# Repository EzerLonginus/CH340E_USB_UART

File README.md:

# CH340E_USB_UART
Simple USB to UART adapter using the CH340E

This board is a simple breakout for the CH340E USB to UART interface chip.  This chip is the less expensive option to the CP2102 or FTDI brand chip sets.  

## Purpose
I am looking to incorporate this chip in some designs, and I wanted to make confirm that this design will work.  It's pretty similar to the chips you would see on [AliExpress](https://www.aliexpress.us/item/3256805368897642.html) and [Ebay](https://www.ebay.com/itm/134189916686).

## Scematic

## Layout

## 3D Render

## Current State of Affairs
### Version 1
* Populate and test board
* Fix the inevitable issue that I missed during production

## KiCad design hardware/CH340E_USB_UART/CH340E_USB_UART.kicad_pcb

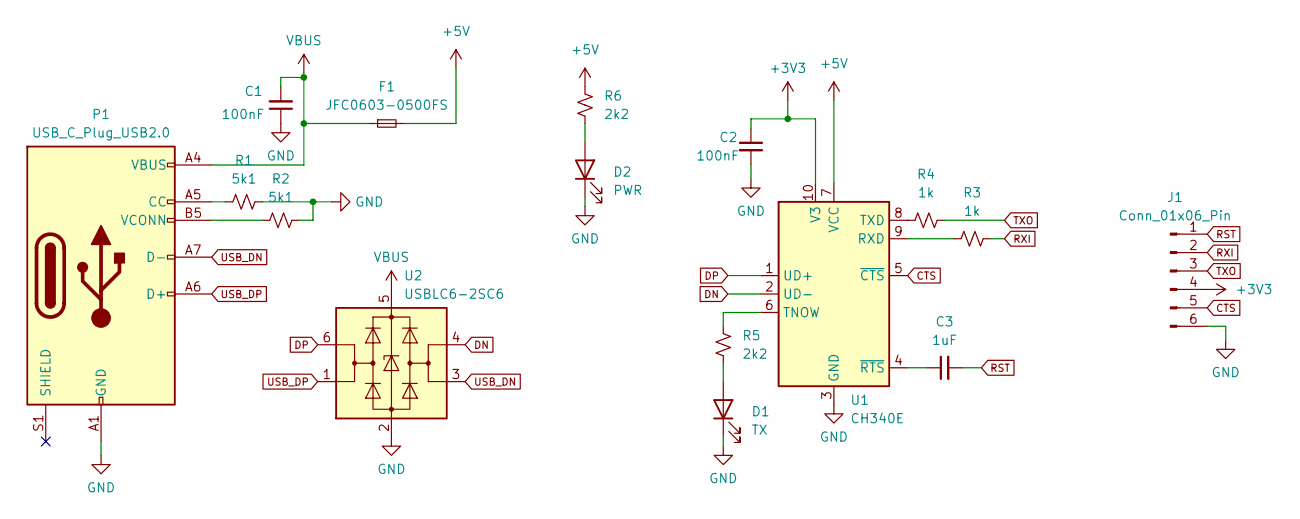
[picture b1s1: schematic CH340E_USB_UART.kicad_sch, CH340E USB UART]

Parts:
C1, C2: 100nF; C_0603_1608Metric
C3: 1uF; C_0603_1608Metric
D1: TX; LED_0603_1608Metric
D2: PWR; LED_0603_1608Metric
F1: JFC0603-0500FS; Fuse_0603_1608Metric
J1: Conn_01x06_Pin; PinHeader_1x06_P2.54mm_Vertical
P1: USB_C_Plug_USB2.0; USB_C_Receptacle_G-Switch_GT-USB-7010ASV
R1, R2: 5k1; R_0603_1608Metric
R3, R4: 1k; R_0603_1608Metric
R5, R6: 2k2; R_0603_1608Metric
U1: CH340E; MSOP-10_3x3mm_P0.5mm
U2: USBLC6-2SC6; SOT-23-6

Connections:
+3V3: C2.1, J1.4, U1.10 (V3)
+5V: F1.2, R6.1, U1.7 (VCC)
CTS: J1.5, U1.5 (~CTS)
DN: U1.2 (UD-), U2.4 (I/O2)
DP: U1.1 (UD+), U2.6 (I/O1)
GND: C1.1, C2.2, D1.1 (K), D2.1 (K), J1.6, P1.A1 (GND), P1.A12 (GND), P1.B1 (GND), P1.B12 (GND), R1.2, R2.2, U1.3 (GND), U2.2 (GND)
unnamed: D1.2 (A), R5.2
unnamed: D2.2 (A), R6.2
unnamed: P1.A5 (CC), R1.1
unnamed: P1.B5 (VCONN), R2.1
unnamed: R3.2, U1.9 (RXD)
unnamed: R5.1, U1.6 (TNOW)
unnamed: R4.2, U1.8 (TXD)
unnamed: C3.1, U1.4 (~RTS)
RST: C3.2, J1.1
RXI: J1.2, R3.1
TXO: J1.3, R4.1
USB_DN: P1.A7 (D-), U2.3 (I/O2)
USB_DP: P1.A6 (D+), U2.1 (I/O1)
VBUS: C1.2, F1.1, P1.A4 (VBUS), P1.A9 (VBUS), P1.B4 (VBUS), P1.B9 (VBUS), U2.5 (VBUS)

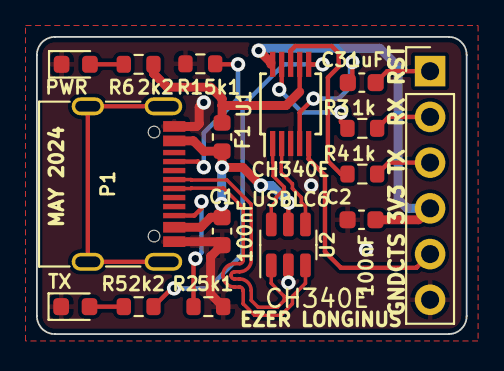
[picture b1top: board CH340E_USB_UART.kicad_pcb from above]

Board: 2 copper layers, 23.9 x 16.5 mm, 16 parts (0 on the bottom side), 20 nets.

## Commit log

2024-05-23 Initial commit for CH340E schematic
